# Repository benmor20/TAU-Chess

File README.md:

# PIE-Final-Project-Chess
## Charlie Babe, Gabby Blake, Carlo Colizzi, Aissa Conde, Ben Morris

A project to create an automatic chess board for learning chess.

### Code Requirements
The Python code needs the following packages to run:
* python-chess
* tensorflow

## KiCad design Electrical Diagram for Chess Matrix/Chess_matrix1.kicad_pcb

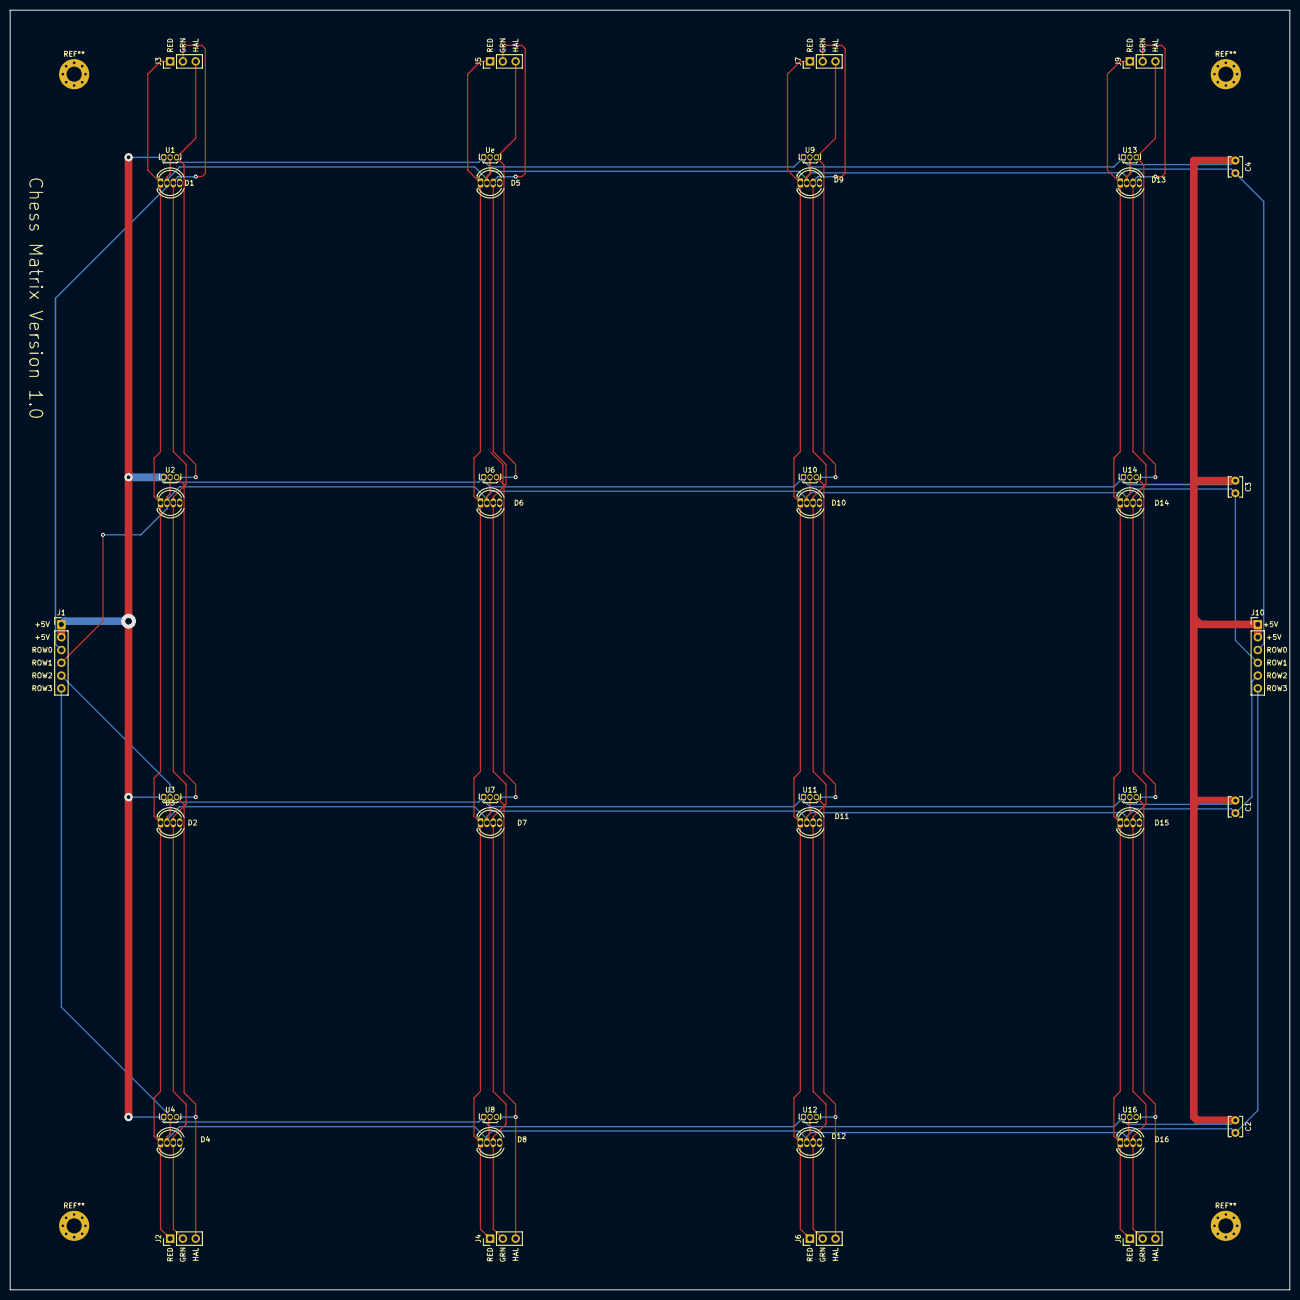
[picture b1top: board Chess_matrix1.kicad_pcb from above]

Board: 2 copper layers, 254.0 x 254.0 mm, 46 parts (0 on the bottom side), 17 nets.

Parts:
C1, C2, C3, C4: 0.1uf; C_Disc_D3.8mm_W2.6mm_P2.50mm
D1, D2, D3, D4, D5, D6, D7, D8, D9, D10, D11, D12, D13, D14, D15, D16: LED_RCGB; LED_D5.0mm-4_RGB
J1, J10: Conn_01x06; PinHeader_1x06_P2.54mm_Vertical
J2, J3, J4, J5, J6, J7, J8, J9: Conn_01x03; PinHeader_1x03_P2.54mm_Vertical
U1, U2, U3, U4, U6, U7, U8, U9, U10, U11, U12, U13, U14, U15, U16: 3144A; TO-92Flat
Ue: 3144A; TO-92Flat

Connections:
+5V: C1.1, C2.1, C3.1, C4.1, J1.1, J1.2, J10.1, J10.2, U1.1, U2.1, U3.1, U4.1, U6.1, U7.1, U8.1, U9.1, U10.1, U11.1, U12.1, U13.1, U14.1, U15.1, U16.1, Ue.1
unnamed: C1.2, D3.2, D7.2, D11.2, D15.2, J1.5, J10.5, U3.2, U7.2, U11.2, U15.2
unnamed: C2.2, D4.2, D8.2, D12.2, D16.2, J1.6, J10.6, U4.2, U8.2, U12.2, U16.2
unnamed: C3.2, D2.2, D6.2, D10.2, D14.2, J1.4, J10.4, U2.2, U6.2, U10.2, U14.2
unnamed: C4.2, D1.2, D5.2, D9.2, D13.2, J1.3, J10.3, U1.2, U9.2, U13.2, Ue.2
unnamed: D1.1, D2.1, D3.1, D4.1, J2.1, J3.1
unnamed: D1.3, D2.3, D3.3, D4.3, J2.2, J3.2
unnamed: D5.1, D6.1, D7.1, D8.1, J4.1, J5.1
unnamed: D5.3, D6.3, D7.3, D8.3, J4.2, J5.2
unnamed: D9.1, D10.1, D11.1, D12.1, J6.1, J7.1
unnamed: D9.3, D10.3, D11.3, D12.3, J6.2, J7.2
unnamed: D13.1, D14.1, D15.1, D16.1, J8.1, J9.1
unnamed: D13.3, D14.3, D15.3, D16.3, J8.2, J9.2
unnamed: J2.3, J3.3, U1.3, U2.3, U3.3, U4.3
unnamed: J4.3, J5.3, U6.3, U7.3, U8.3, Ue.3
unnamed: J6.3, J7.3, U9.3, U10.3, U11.3, U12.3
unnamed: J8.3, J9.3, U13.3, U14.3, U15.3, U16.3

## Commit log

2021-10-28 Add files via upload
    Chess Pieces with holes for magnets
2021-10-28 Added STL files of each chess piece
2021-11-01 CADded all mounts for the gantry system
2021-11-01 Minor repo organization
2021-11-01 Added communication library
2021-11-01 Added arduino serial connection, updated for steppers
2021-11-01 Imported version 1
    Currently tensorflow is not cooperating and the data is not properly imported
2021-11-04 Created code to control step motor for sprint 1
2021-11-04 updated test stepper code
2021-11-04 added Cad chess pieces
2021-11-04 removed extra chess piece folder
2021-11-05 Create Surface Chess Board.SLDPRT
    Added Surface board
2021-11-08 added cad files
2021-11-08 added cad files from mcmaster and started gantry assembly
2021-11-08 Update Surface Chess Board.SLDPRT
    Updates Surface Board with refrerence holes
2021-11-08 Made Bottom Chess Board
2021-11-10 Finished Gantry Assembly
2021-11-10 Added Full Sprint 2 Assembly
2021-11-10 created stl
2021-11-11 updated pieces and simple test stepper code
2021-11-15 Stepper motor integration
2021-11-15 Created chess engine code
2021-11-15 created empty method for later arduino interfacing
2021-11-16 Updates Hole Sizes
2021-11-18 created stl files for chess pieces
2021-11-19 Start stepper control
2021-11-24 Steppers through python
2021-11-26 DigitalOutput (magnet) working
2021-11-29 Removed extra logging
2021-11-29 Updated drive_system
2021-11-29 Created path-piecing method
2021-12-02 Hall effect matrix in python, slight reorganization
    Note: still need to figure out the correct order of ports for matrix
2021-12-06 Matrix pins in right order, ensured 2 arduinos work
2021-12-06 fixed chess engine
2021-12-06 Create ~$Bottom Chess Board.SLDPRT
    Dimension change
2021-12-06 CAD
    Added new side dimensions
2021-12-08 Set theme jekyll-theme-cayman
2021-12-08 Made moversensor, chess engine updates
2021-12-09 Test code
2021-12-09 tested stuff
2021-12-09 Updated CAD Files
2021-12-10 CAD Updates
2021-12-10 Update move sensor, testing
2021-12-11 controller fixes
2021-12-11 Diagonal motion!
2021-12-11 created graphics
2021-12-12 did some motor testing
2021-12-14 Day before changes
2021-12-14 Demo day changes
2021-12-14 Clean up
